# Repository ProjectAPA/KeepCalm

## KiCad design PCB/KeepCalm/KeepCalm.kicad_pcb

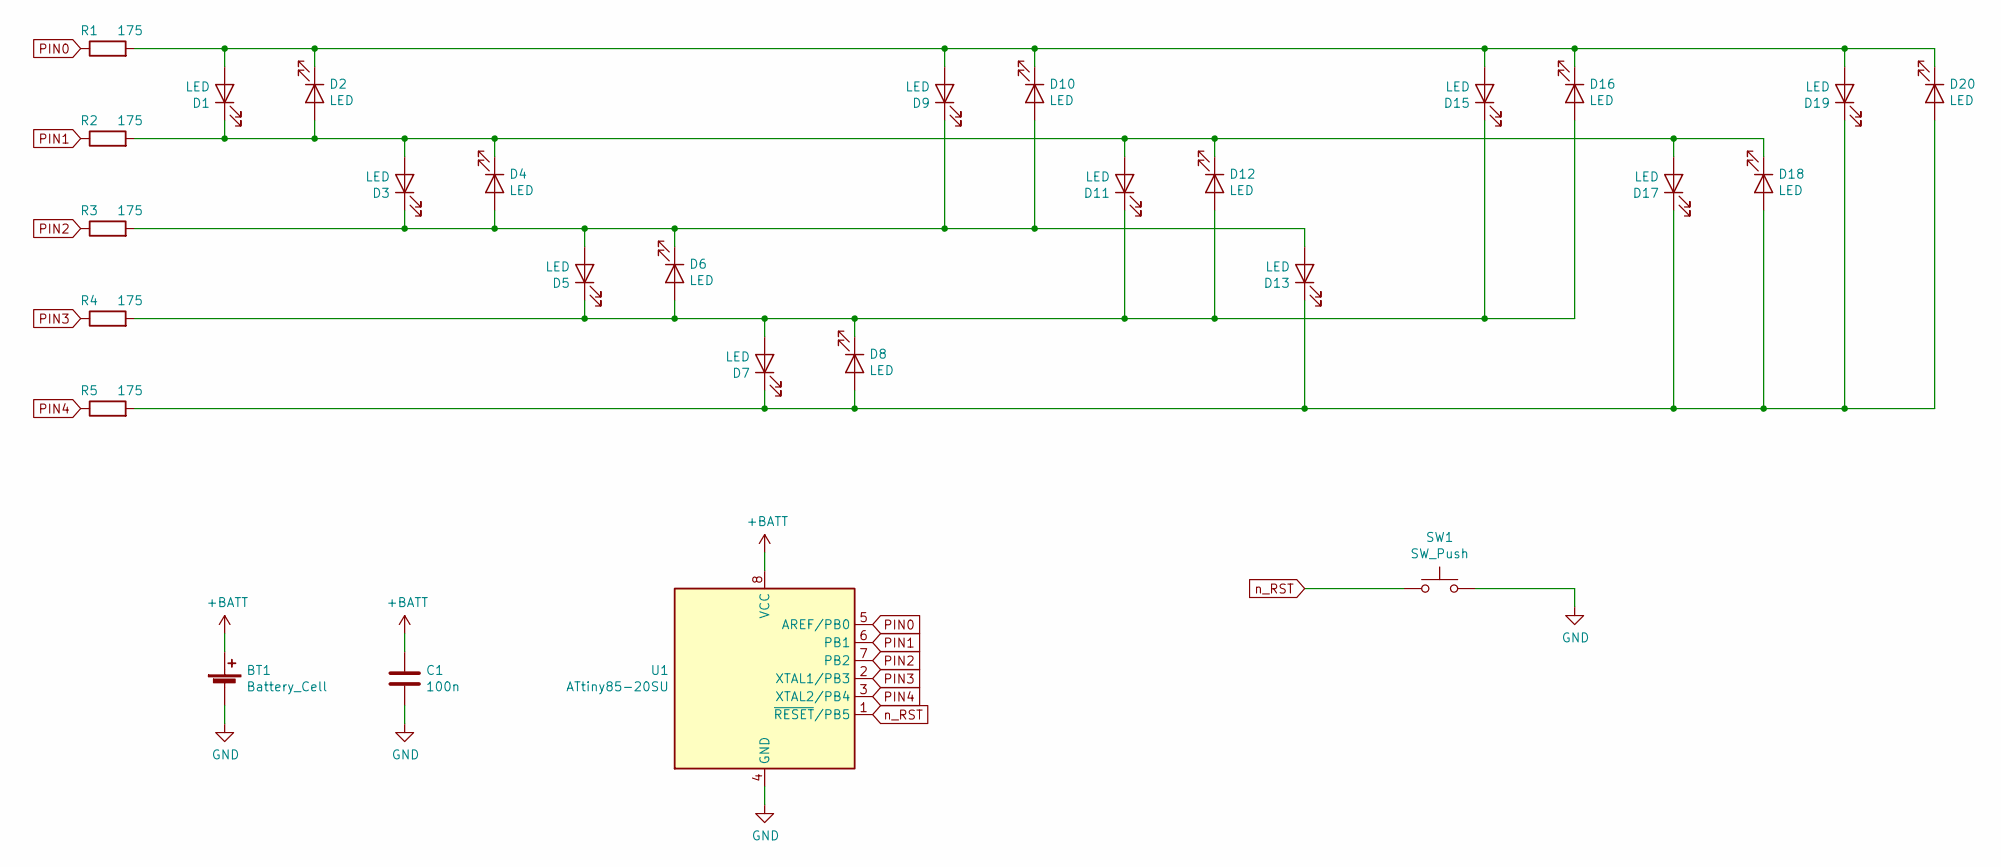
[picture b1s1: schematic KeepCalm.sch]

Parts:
BT1: Battery_Cell; BatteryHolder_Keystone_1060_1x2032
C1: 100n; C_0805_2012Metric_Pad1.15x1.40mm_HandSolder
D1, D2, D3, D4, D5, D6, D7, D8, D9, D10, D11, D12, D13, D15, D16, D17, D18, D19, D20: LED; LED_0805_2012Metric_Pad1.15x1.40mm_HandSolder
R1, R2, R3, R4, R5: 175; R_0805_2012Metric_Pad1.15x1.40mm_HandSolder
SW1: SW_Push; SW_Push_1P1T_NO_6x6mm_H9.5mm
U1: ATtiny85-20SU; SOIJ-8_5.3x5.3mm_P1.27mm

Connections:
+BATT: BT1.1 (+), C1.1, U1.8 (VCC)
GND: BT1.2 (-), C1.2, SW1.2, U1.4 (GND)
unnamed: D1.1 (K), D2.2 (A), D3.2 (A), D4.1 (K), D11.2 (A), D12.1 (K), D17.2 (A), D18.1 (K), R2.2
unnamed: D1.2 (A), D2.1 (K), D9.2 (A), D10.1 (K), D15.2 (A), D16.1 (K), D19.2 (A), D20.1 (K), R1.2
unnamed: D3.1 (K), D4.2 (A), D5.2 (A), D6.1 (K), D9.1 (K), D10.2 (A), D13.2 (A), R3.2
unnamed: D5.1 (K), D6.2 (A), D7.2 (A), D8.1 (K), D11.1 (K), D12.2 (A), D15.1 (K), D16.2 (A), R4.2
unnamed: D7.1 (K), D8.2 (A), D13.1 (K), D17.1 (K), D18.2 (A), D19.1 (K), D20.2 (A), R5.2
PIN0: R1.1, U1.5 (AREF/PB0)
PIN1: R2.1, U1.6 (PB1)
PIN2: R3.1, U1.7 (PB2)
PIN3: R4.1, U1.2 (XTAL1/PB3)
PIN4: R5.1, U1.3 (XTAL2/PB4)
n_RST: SW1.1, U1.1 (~RESET~/PB5)

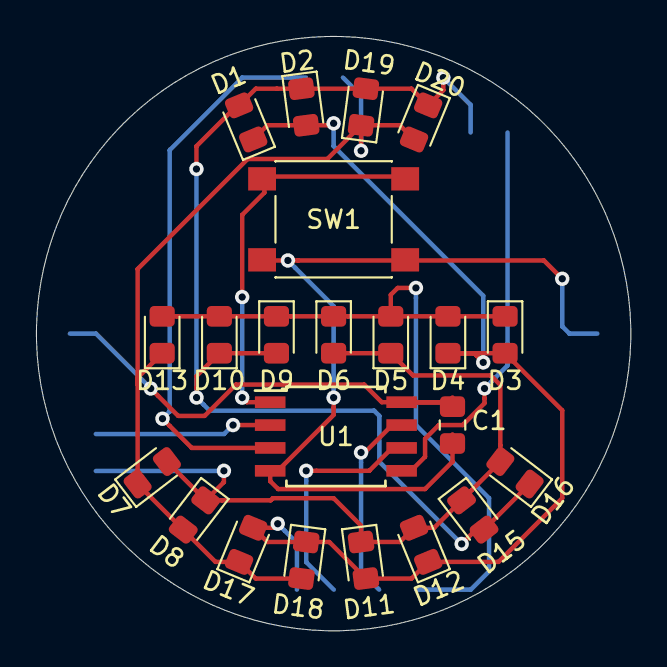
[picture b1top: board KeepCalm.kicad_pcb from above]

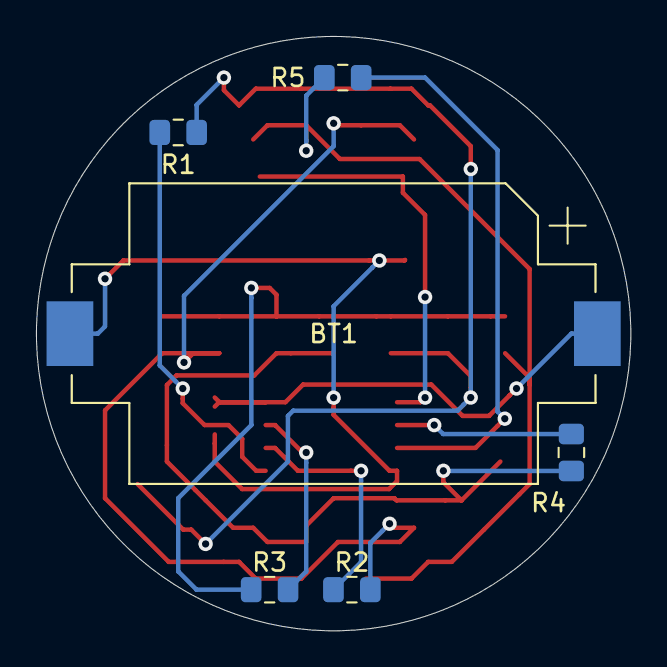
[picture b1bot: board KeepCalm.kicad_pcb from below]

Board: 2 copper layers, 33.0 x 33.0 mm, 28 parts (6 on the bottom side), 13 nets.

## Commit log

2020-01-27 Added gitingnore
2020-01-27 experimenting with pwm
2020-01-27 PWM Changes
2020-01-28 inital Commit
2020-01-31 Added PCB for New Design
2020-01-31 Final Changes To PCB
2020-01-31 Top Plate CAD
2020-02-09 Improved CAD
2020-02-09 Basic Led Struct
2020-02-10 Added Timer for led control
2020-02-10 Implemented full LED control
2020-02-11 Added led timing
2020-02-26 Basic Function
2020-02-26 Tested with Timer0
2020-02-26 Cleaned up
2020-02-28 New CAD Desgin
2020-02-28 Added Low Power
